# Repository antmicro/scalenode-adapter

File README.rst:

=================
Scalenode Adapter
=================

Copyright (c) 2021 `Antmicro <https://www.antmicro.com>`_

.. figure:: img/scalenode-adapter.png

Overview
--------

This repository contains design files of the expansion card for the Antmicro's `Scalenode <https://github.com/antmicro/scalenode>`_ platform.
This expansion card exposes three USB host ports with independent supply current monitoring for each port.
This allows for using the Scalenode to interact with external, FPGA-driven evaluation boards such as the Digilent `Arty A7 <https://reference.digilentinc.com/programmable-logic/arty/start>`_ boards.
The design files were prepared in KiCad.
An initial production release for the design was fabricated as prototypes and these are now being tested.

Repository structure
--------------------
The main repository directory contains KiCad PCB project files, a LICENSE and README.
The remaining files are stored in the following directories:

* ``lib`` - contains the component libraries
* ``img`` - contains graphics for this README

Key Features
------------

* Expansion board for the Scalenode module
* Supports up to three Digilet Arty boards
* On-board current measurement circuitry

License
=======

`Apache-2.0 <LICENSE>`_

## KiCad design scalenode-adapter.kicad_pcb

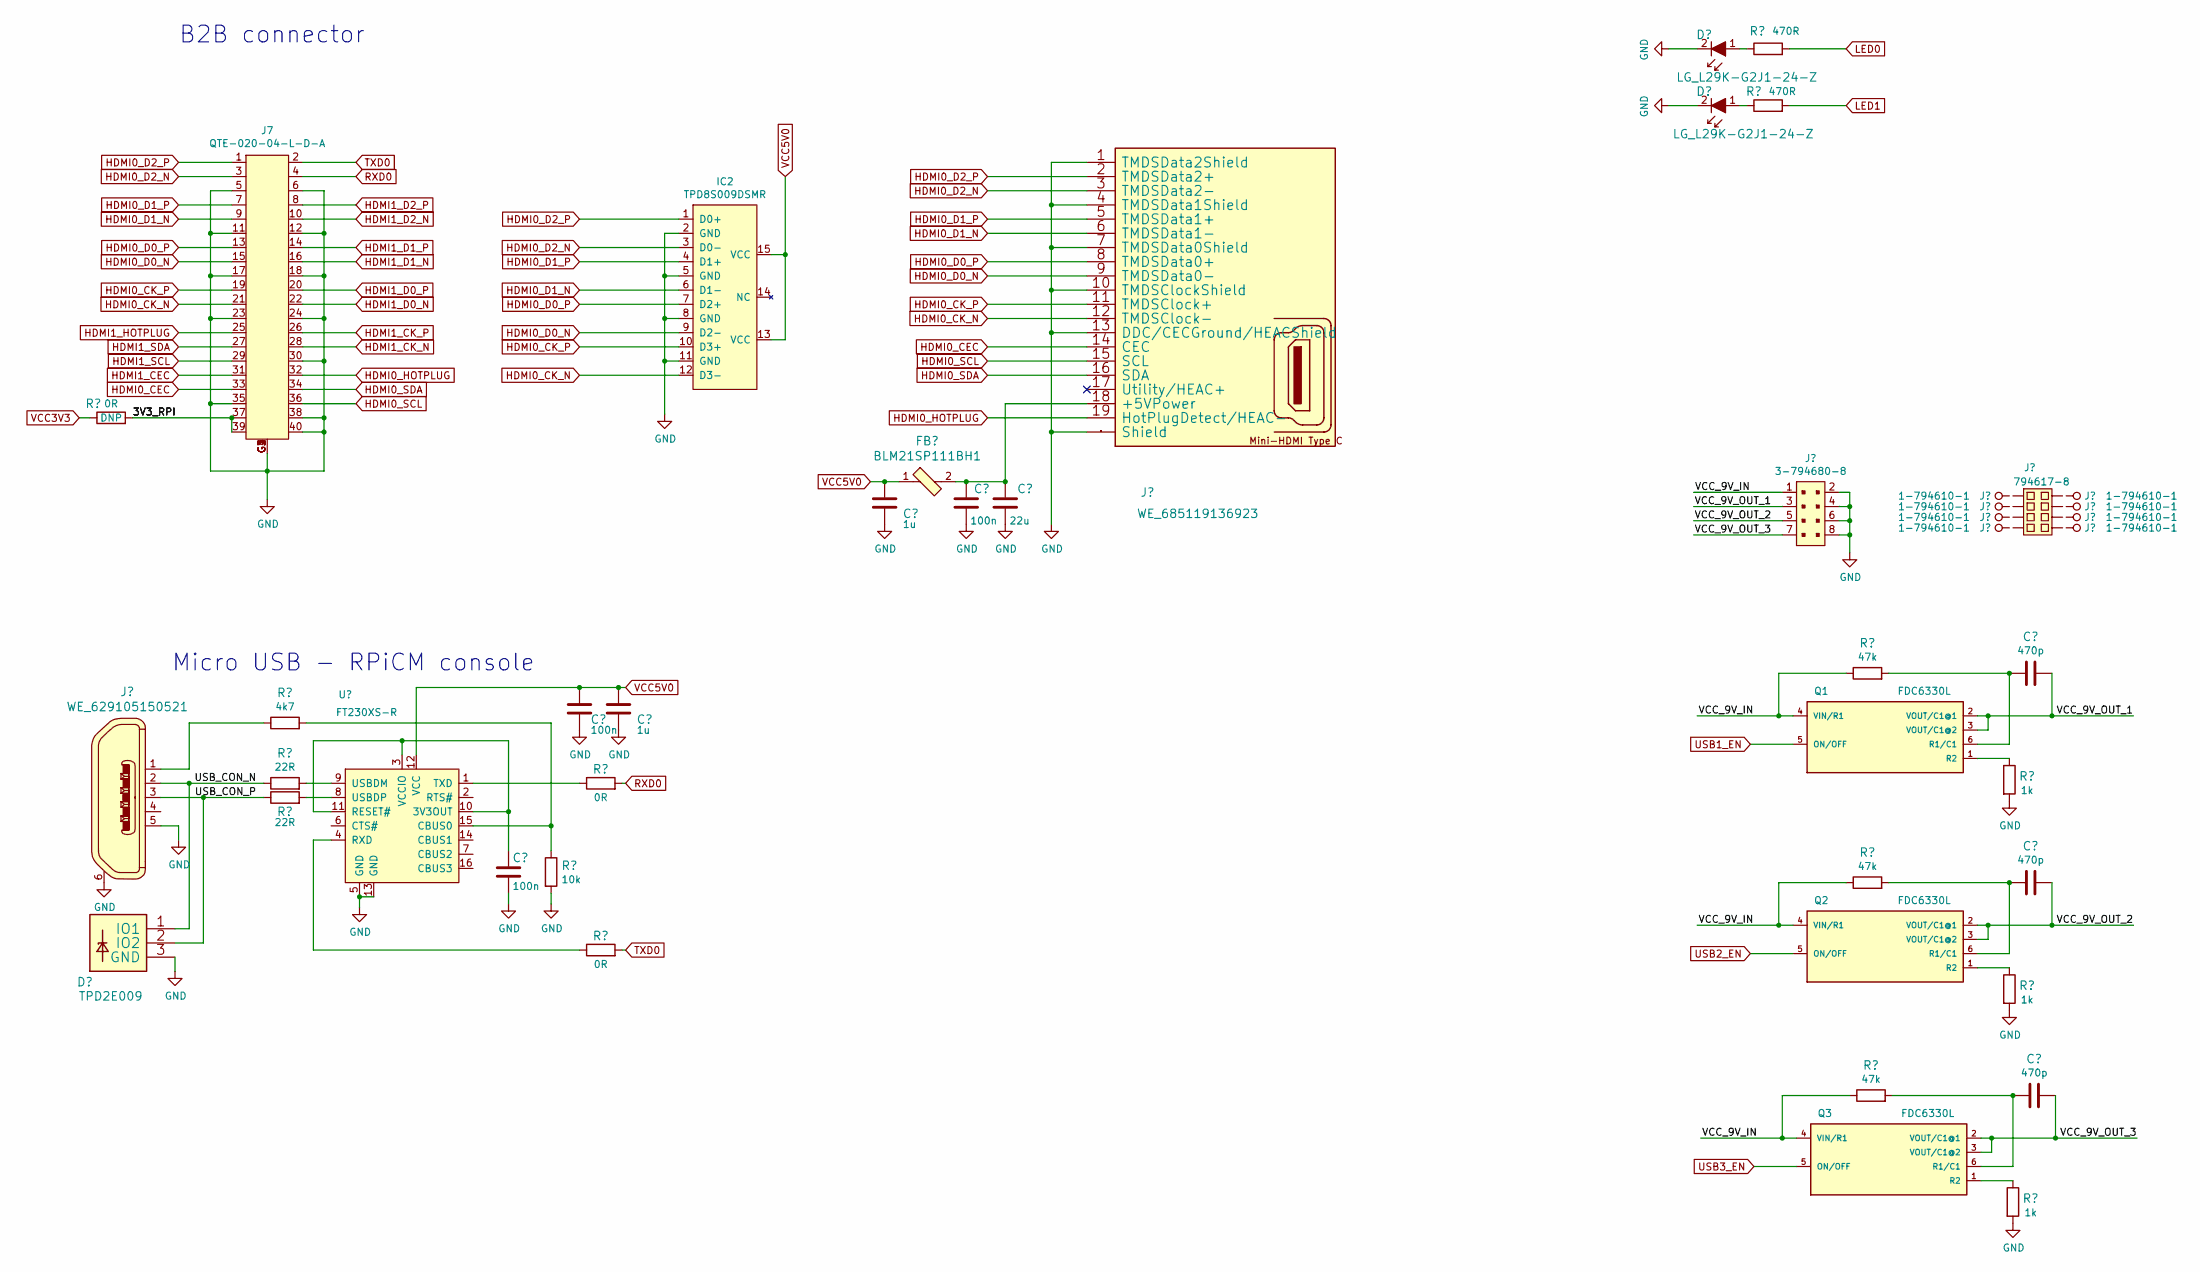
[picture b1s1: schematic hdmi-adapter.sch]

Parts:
C49, C50, C53: C_100n_0402; 0402-cap; MPN 0402X104K6R3CT
C51, C52: C_1u_0402; 0402-cap; MPN C1005X6S1A105K050BC
C54: C_22u_0603; 0603-cap; MPN GRM188R60J226MEA0D
D8, D9: LG_L29K-G2J1-24-Z; LED_0603; MPN LG L29K-G2J1-24-Z
D10: TPD2E009; SOT-3; MPN TPD2E009DRTR
FB2: BLM21SP111BH1; 0805-res; MPN BLM21SP111BH1D
IC2: TPD8S009DSMR; R-PDSO-N15; MPN TPD8S009DSMR
J7: QTE-020-04-L-D-A; MPN QTE-020-04-L-D-A
J8: WE_629105150521; USB_Micro_B_Female_629105150521; MPN 629105150521
Q1, Q2, Q3: FDC6330L; MPN FDC6330L
R37: R_0R_0805; 0805-res; MPN CRCW08050000Z0EA
R38, R39: R_470R_0402; 0402-res; MPN CRCW0402470RFKED
R47, R48, R49: R_1k_0402; 0402-res; MPN CR0402-FX-1001GLF

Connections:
/antartix hdmi adapter/3V3_RPI: J7.37, J7.39, R37.2
/antartix hdmi adapter/USB_CON_N: D10.1 (IO1), J8.2; also elsewhere on the board
/antartix hdmi adapter/USB_CON_P: D10.2 (IO2), J8.3; also elsewhere on the board
/antartix hdmi adapter/VCC_9V_IN: Q1.4 (VIN/R1), Q2.4 (VIN/R1), Q3.4 (VIN/R1); also elsewhere on the board
/antartix hdmi adapter/VCC_9V_OUT_1: Q1.2 (VOUT/C1@1), Q1.3 (VOUT/C1@2); also elsewhere on the board
/antartix hdmi adapter/VCC_9V_OUT_2: Q2.2 (VOUT/C1@1), Q2.3 (VOUT/C1@2); also elsewhere on the board
/antartix hdmi adapter/VCC_9V_OUT_3: Q3.2 (VOUT/C1@1), Q3.3 (VOUT/C1@2); also elsewhere on the board
GND: C49.2, C50.2, C51.2, C52.2, C53.2, C54.1, D8.2, D9.2, D10.3 (GND), IC2.2 (GND), IC2.5 (GND), IC2.8 (GND), IC2.11 (GND), J7.5, J7.6, J7.11, J7.12, J7.17, J7.18, J7.23, J7.24, J7.30, J7.35, J7.38, J7.40, J7.G1, J7.G2, J7.G3, J7.G4, J8.5, J8.6, R47.2, R48.2, R49.2; also elsewhere on the board
HDMI0_CEC: J7.33; also elsewhere on the board
HDMI0_CK_N: IC2.12 (D3-), J7.21; also elsewhere on the board
HDMI0_CK_P: IC2.10 (D3+), J7.19; also elsewhere on the board
HDMI0_D0_N: IC2.9 (D2-), J7.15; also elsewhere on the board
HDMI0_D0_P: IC2.7 (D2+), J7.13; also elsewhere on the board
HDMI0_D1_N: IC2.6 (D1-), J7.9; also elsewhere on the board
HDMI0_D1_P: IC2.4 (D1+), J7.7; also elsewhere on the board
HDMI0_D2_N: IC2.3 (D0-), J7.3; also elsewhere on the board
HDMI0_D2_P: IC2.1 (D0+), J7.1; also elsewhere on the board
HDMI0_HOTPLUG: J7.32; also elsewhere on the board
HDMI0_SCL: J7.36; also elsewhere on the board
HDMI0_SDA: J7.34; also elsewhere on the board
HDMI1_CEC: J7.31
HDMI1_CK_N: J7.28
HDMI1_CK_P: J7.26
HDMI1_D0_N: J7.22
HDMI1_D0_P: J7.20
HDMI1_D1_N: J7.16
HDMI1_D1_P: J7.14
HDMI1_D2_N: J7.10
HDMI1_D2_P: J7.8
HDMI1_HOTPLUG: J7.25
HDMI1_SCL: J7.29
HDMI1_SDA: J7.27
LED0: R38.2; also elsewhere on the board
LED1: R39.2; also elsewhere on the board
unnamed 66: C49.1; also elsewhere on the board
unnamed 67: C53.1, C54.2, FB2.2; also elsewhere on the board
unnamed 68: Q1.6 (R1/C1); also elsewhere on the board
unnamed 69: Q2.6 (R1/C1); also elsewhere on the board
unnamed 70: Q3.6 (R1/C1); also elsewhere on the board
unnamed: D8.1, R38.1
unnamed: D9.1, R39.1
unnamed 124: J8.1; also elsewhere on the board
unnamed: Q1.1 (R2), R47.1
unnamed: Q2.1 (R2), R48.1
unnamed: Q3.1 (R2), R49.1
RXD0: J7.4; also elsewhere on the board
TXD0: J7.2; also elsewhere on the board
USB1_EN: Q1.5 (ON/OFF); also elsewhere on the board
USB2_EN: Q2.5 (ON/OFF); also elsewhere on the board
USB3_EN: Q3.5 (ON/OFF); also elsewhere on the board
VCC3V3: R37.1; also elsewhere on the board
VCC5V0: C50.1, C51.1, C52.1, FB2.1, IC2.13 (VCC), IC2.15 (VCC); also elsewhere on the board

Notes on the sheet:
B2B connector
Micro USB - RPiCM console

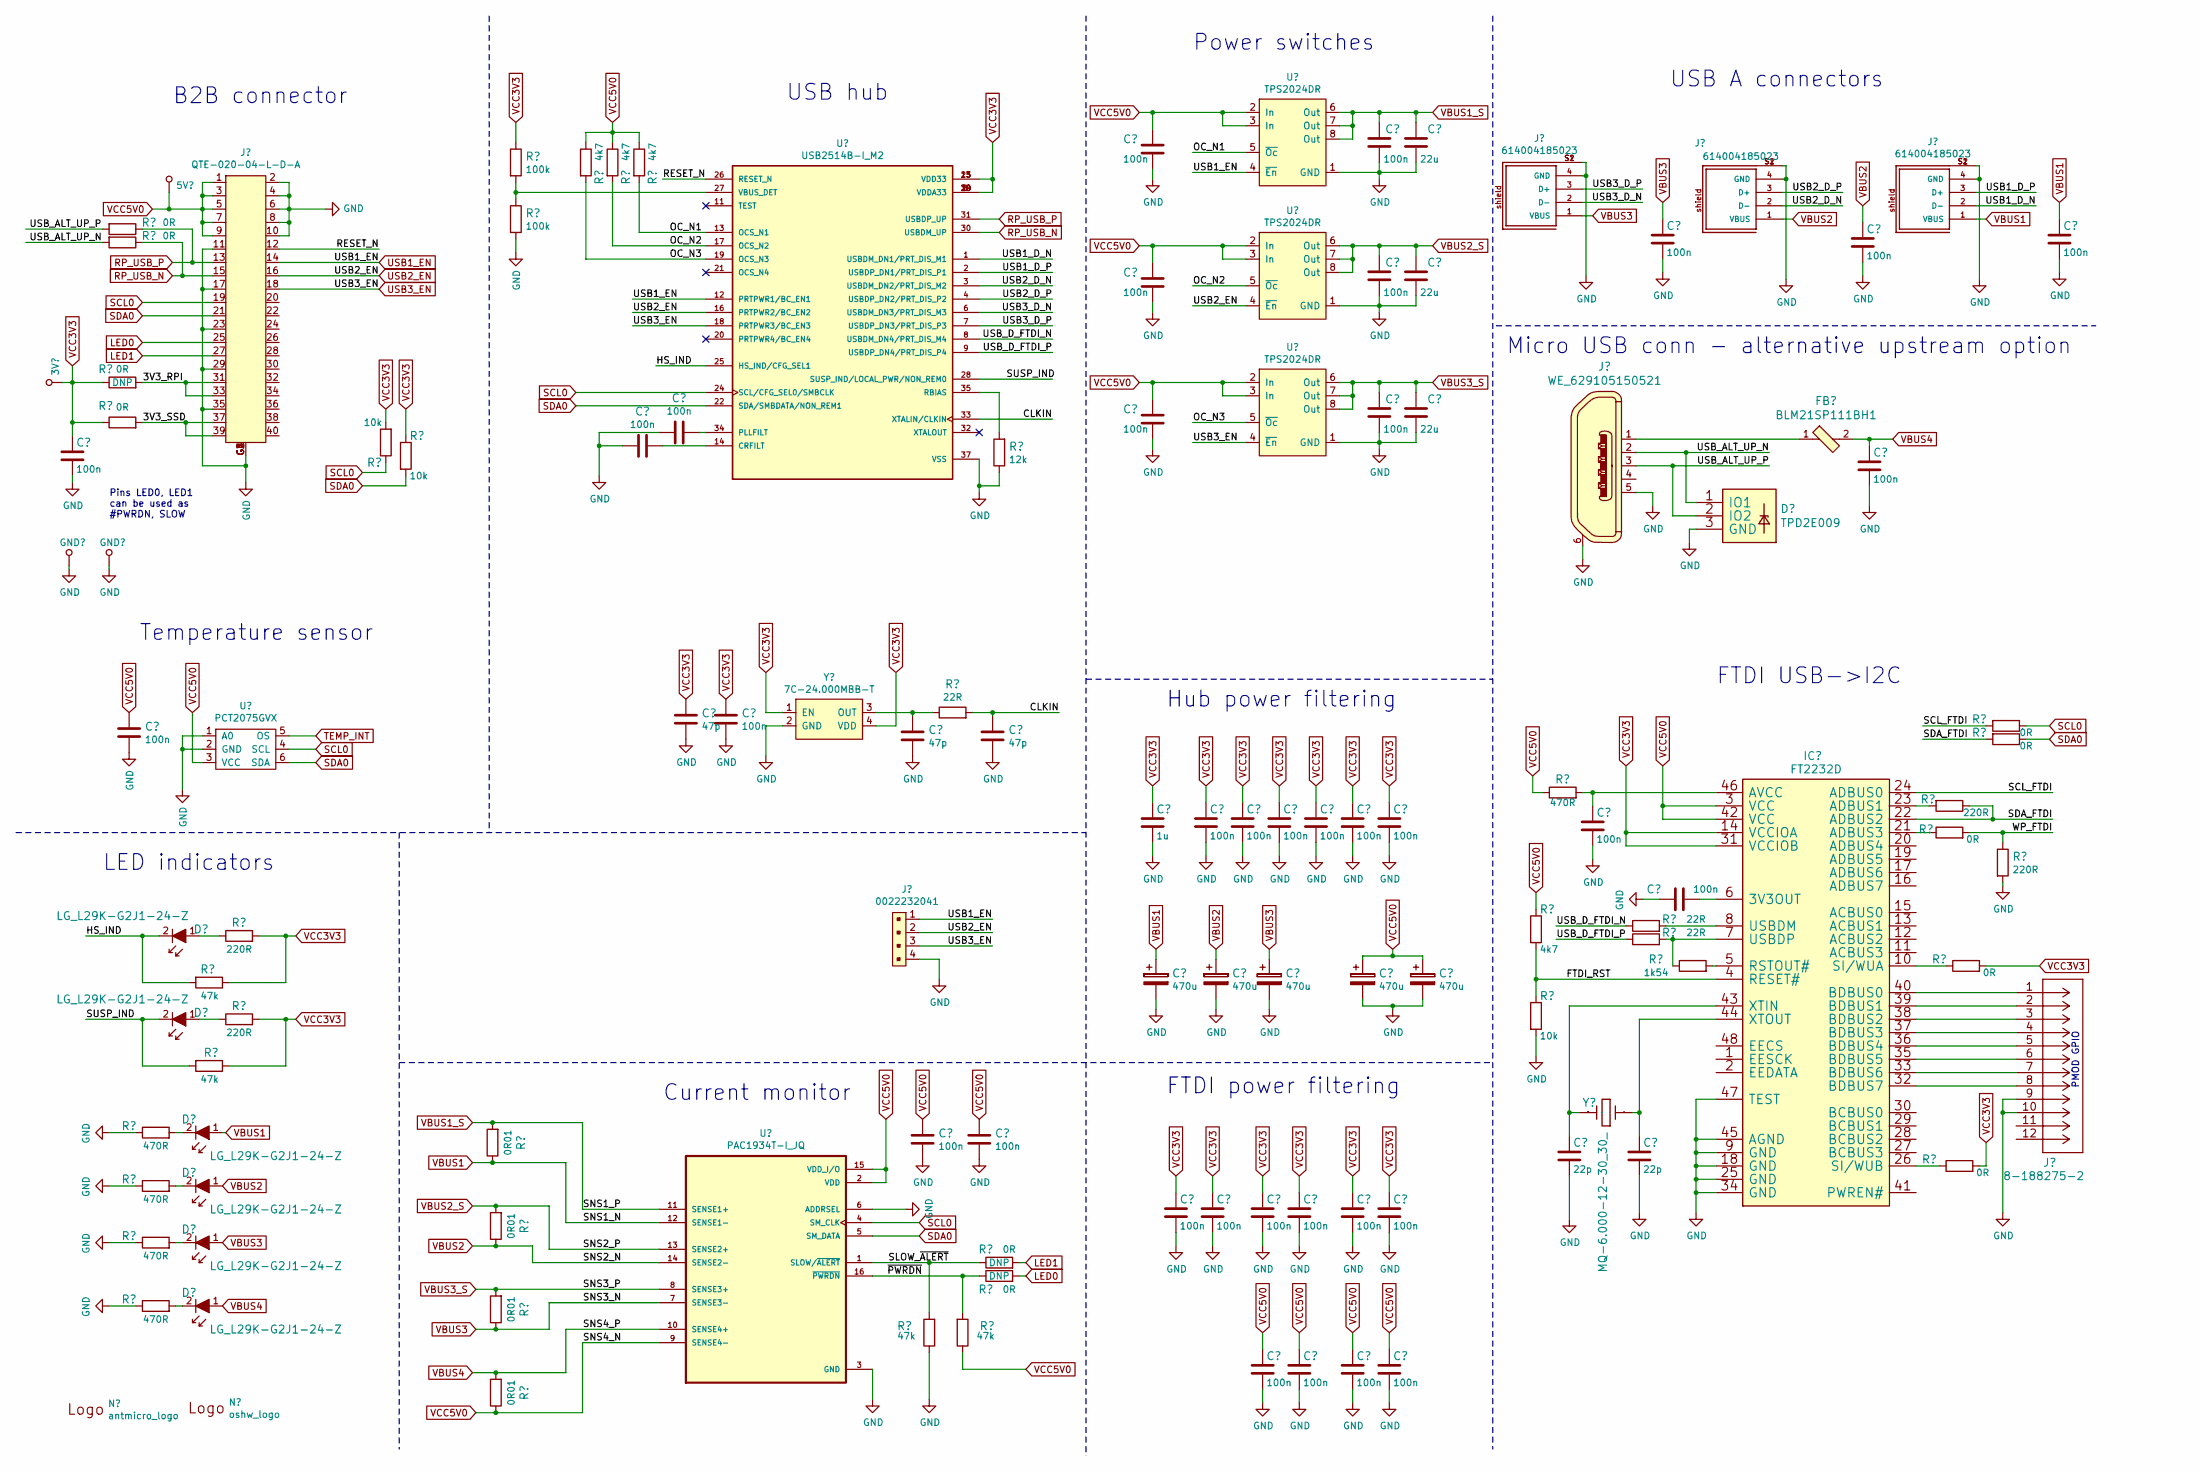
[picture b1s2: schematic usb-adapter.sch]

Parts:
3V1, 5V1: TP_SMD1MM; Testpoint_smd_1mm
C1, C2, C3, C4, C6, C9, C15, C16, C17, C19, C20, C21, C23, C24, C25, C26, C27, C28, C29, C31, C32, C33, C34, C35, C36, C42, C44, C45, C46, C47, C48, C58: C_100n_0402; 0402-cap; MPN 0402X104K6R3CT
C5, C7, C8: C_47p_0402; 0402-cap; MPN C0402C470J5GACTU
C10, C11, C12: C_100n_0603; 0603-cap; MPN 0603YC104KAZ2A
C13: C_1u_0402; 0402-cap; MPN C1005X6S1A105K050BC
C14, C18, C22, C30, C40: C_470u_KEMET_D; KEMET_D; MPN TR3D477M6R3C0200
C37, C38, C39: C_22u_0603; 0603-cap; MPN GRM188R60J226MEA0D
C41, C43: C_22p_0402; 0402-cap; MPN CC0402JRNPO9BN220
D1, D2, D3, D4, D5, D6: LG_L29K-G2J1-24-Z; LED_0603; MPN LG L29K-G2J1-24-Z
D7: TPD2E009; SOT-3; MPN TPD2E009DRTR
FB1: BLM21SP111BH1; 0805-res; MPN BLM21SP111BH1D
GND1, GND2: TP_SMD1MM; Testpoint_smd_1mm
IC1: FT2232D; LQFP-48_7x7mm; MPN FT2232D-REEL
J1: QTE-020-04-L-D-A; MPN QTE-020-04-L-D-A
J2: 0022232041; PinHeader_1x4_P2.54mm_Drill1.02mm; MPN 0022232041
J3, J5, J6: 614004185023; MPN 614004185023
J4: WE_629105150521; USB_Micro_B_Female_629105150521; MPN 629105150521
N1: antmicro_logo; antmicro-logo_scaled_15mm
N2: oshw_logo; oshw-logo
R1, R2, R31, R32, R33, R35, R36: R_0R_0402; 0402-res; MPN ERJ2GE0R00X
R3, R4: R_0R_0805; 0805-res; MPN CRCW08050000Z0EA
R5, R6, R7, R8, R28: R_470R_0402; 0402-res; MPN CRCW0402470RFKED
R9, R10, R50, R51: R_47k_0402; 0402-res; MPN MCMR04X4702FTL
R11, R12, R30, R34: R_220R_0402; 0402-res; MPN ERJ2GEJ221X
R13, R14, R27: R_10k_0402; 0402-res; MPN CRCW040210K0FKEDHP
R15, R16, R21, R22: R_0R01_1206; 1206-res; MPN ERJMP2KF10MU
R17, R18: R_100k_0402; 0402-res; MPN CRCW0402100KFKEDHP
R19, R20, R23, R26: R_4k7_0402; 0402-res; MPN ERJ2GEJ472X
R24, R56, R57: R_22R_0402; 0402-res; MPN CRCW040222R0FKED
R25: R_12k_0402; 0402-res; MPN CRCW040212K0FKEDHP
R29: R_1k54_0402; 0402-res; MPN CRCW04021K54FKED.
U1: PCT2075GVX; SOT95P275X110-6N; MPN PCT2075GVX
U2: PAC1934T-I_JQ; QFN65P400X400X55-17N
U3: USB2514B-I_M2; QFN50P600X600X100-37N; MPN USB2514B-I/M2
U4, U5, U6: TPS2024DR; SOIC-8_W3.9mm; MPN TPS2024DR
Y1: 7C-24.000MBB-T; MPN 7C-24.000MBB-T
Y2: MQ-6.000-12-30_30_; Crystal_5x7mm; MPN MQ-6.000-12-30/30/-40+85

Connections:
/antartix usb adapter/3V3_RPI: J1.31, J1.33, R3.2
/antartix usb adapter/3V3_SSD: J1.37, J1.39, R4.2
/antartix usb adapter/CLKIN: C8.1, R24.2, U3.33 (XTALIN/CLKIN)
/antartix usb adapter/FTDI_RST: IC1.4 (RESET#), R26.2, R27.1
/antartix usb adapter/HS_IND: D1.2, R9.2, U3.25 (HS_IND/CFG_SEL1)
/antartix usb adapter/OC_N1: R23.2, U3.13 (OCS_N1), U4.5 (~Oc)
/antartix usb adapter/OC_N2: R20.2, U3.17 (OCS_N2), U5.5 (~Oc)
/antartix usb adapter/OC_N3: R19.2, U3.19 (OCS_N3), U6.5 (~Oc)
/antartix usb adapter/RESET_N: J1.12, U3.26 (RESET_N)
/antartix usb adapter/SCL_FTDI: IC1.24 (ADBUS0), R35.2
/antartix usb adapter/SDA_FTDI: IC1.22 (ADBUS2), R30.1, R36.2
/antartix usb adapter/SLOW_~ALERT: R50.2, U2.1 (SLOW/~ALERT); also elsewhere on the board
/antartix usb adapter/SUSP_IND: D2.2, R10.2, U3.28 (SUSP_IND/LOCAL_PWR/NON_REM0)
/antartix usb adapter/USB1_D_N: J6.2 (D-), U3.1 (USBDM_DN1/PRT_DIS_M1)
/antartix usb adapter/USB1_D_P: J6.3 (D+), U3.2 (USBDP_DN1/PRT_DIS_P1)
/antartix usb adapter/USB2_D_N: J5.2 (D-), U3.3 (USBDM_DN2/PRT_DIS_M2)
/antartix usb adapter/USB2_D_P: J5.3 (D+), U3.4 (USBDP_DN2/PRT_DIS_P2)
/antartix usb adapter/USB3_D_N: J3.2 (D-), U3.6 (USBDM_DN3/PRT_DIS_M3)
/antartix usb adapter/USB3_D_P: J3.3 (D+), U3.7 (USBDP_DN3/PRT_DIS_P3)
/antartix usb adapter/USB_ALT_UP_N: D7.1 (IO1), J4.2, R2.2
/antartix usb adapter/USB_ALT_UP_P: D7.2 (IO2), J4.3, R1.2
/antartix usb adapter/USB_D_FTDI_N: R56.1, U3.8 (USBDM_DN4/PRT_DIS_M4)
/antartix usb adapter/USB_D_FTDI_P: R57.1, U3.9 (USBDP_DN4/PRT_DIS_P4)
/antartix usb adapter/WP_FTDI: R31.2, R34.1
/antartix usb adapter/~PWRDN: R51.2, U2.16 (~PWRDN); also elsewhere on the board
GND: C1.2, C2.2, C3.2, C4.2, C5.2, C6.2, C7.2, C8.2, C9.2, C10.2, C11.2, C12.2, C13.2, C14.2, C15.2, C16.2, C17.2, C18.2, C19.2, C20.2, C21.2, C22.2, C23.2, C24.2, C25.2, C26.2, C27.2, C28.2, C29.2, C30.2, C31.1, C32.1, C33.1, C34.2, C35.2, C36.2, C37.1, C38.1, C39.1, C40.2, C41.2, C42.2, C43.2, C44.2, C45.2, C46.2, C47.2, C48.2, C58.2, D7.3 (GND), GND1.1, GND2.1, IC1.9 (GND), IC1.18 (GND), IC1.25 (GND), IC1.34 (GND), IC1.45 (AGND), IC1.47 (TEST), J1.2, J1.4, J1.6, J1.8, J1.10, J1.11, J1.17, J1.23, J1.29, J1.35, J1.G1, J1.G2, J1.G3, J1.G4, J2.4, J3.4 (GND), J3.S1, J3.S2, J4.5, J4.6, J5.4 (GND), J5.S1, J5.S2, J6.4 (GND), J6.S1, J6.S2, R5.1, R6.1, R7.1, R8.1, R18.2, R25.1, R27.2, R34.2, R50.1, U1.1 (A0), U1.2 (GND), U2.3 (GND), U2.6 (ADDRSEL), U2.17, U3.37 (VSS), U4.1 (GND), U5.1 (GND), U6.1 (GND), Y1.2 (GND); also elsewhere on the board
LED0: J1.25; also elsewhere on the board
LED1: J1.27; also elsewhere on the board
unnamed: C3.1, U3.14 (CRFILT)
unnamed: C4.1, U3.34 (PLLFILT)
unnamed: C7.1, R24.1, Y1.3 (OUT)
unnamed: C41.1, IC1.43 (XTIN), Y2.1
unnamed: C42.1, IC1.46 (AVCC), R28.2
unnamed: C43.1, IC1.44 (XTOUT), Y2.3
unnamed: C45.1, IC1.6 (3V3OUT)
unnamed: D1.1, R11.1
unnamed: D2.1, R12.1
unnamed: D3.2, R5.2
unnamed: D4.2, R6.2
unnamed: D5.2, R7.2
unnamed: D6.2, R8.2
unnamed: FB1.1, J4.1
unnamed: IC1.5 (RSTOUT#), R29.2
unnamed: IC1.7 (USBDP), R29.1, R57.2
unnamed: IC1.8 (USBDM), R56.2
unnamed: IC1.10 (SI/WUA), R33.1
unnamed: IC1.21 (ADBUS3), R31.1
unnamed: IC1.23 (ADBUS1), R30.2
unnamed: IC1.26 (SI/WUB), R32.1
unnamed 101: IC1.32 (BDBUS7); also elsewhere on the board
unnamed 102: IC1.33 (BDBUS6); also elsewhere on the board
unnamed 103: IC1.35 (BDBUS5); also elsewhere on the board
unnamed 104: IC1.36 (BDBUS4); also elsewhere on the board
unnamed 105: IC1.37 (BDBUS3); also elsewhere on the board
unnamed 106: IC1.38 (BDBUS2); also elsewhere on the board
unnamed 107: IC1.39 (BDBUS1); also elsewhere on the board
unnamed 108: IC1.40 (BDBUS0); also elsewhere on the board
unnamed: R17.2, R18.1, U3.27 (VBUS_DET)
unnamed: R25.2, U3.35 (RBIAS)
RP_USB_N: J1.15, R2.1, U3.30 (USBDM_UP)
RP_USB_P: J1.13, R1.1, U3.31 (USBDP_UP)
SCL0: J1.19, R13.1, R35.1, U1.4 (SCL), U2.4 (SM_CLK), U3.24 (SCL/CFG_SEL0/SMBCLK)
SDA0: J1.21, R14.2, R36.1, U1.6 (SDA), U2.5 (SM_DATA), U3.22 (SDA/SMBDATA/NON_REM1)
TEMP_INT: U1.5 (OS)
USB1_EN: J1.14, J2.1, U3.12 (PRTPWR1/BC_EN1), U4.4 (~En); also elsewhere on the board
USB2_EN: J1.16, J2.2, U3.16 (PRTPWR2/BC_EN2), U5.4 (~En); also elsewhere on the board
USB3_EN: J1.18, J2.3, U3.18 (PRTPWR3/BC_EN3), U6.4 (~En); also elsewhere on the board
VBUS1: C14.1, C48.1, D3.1, J6.1 (VBUS), R15.1, U2.12 (SENSE1-)
VBUS1_S: C31.2, C37.2, R15.2, U2.11 (SENSE1+), U4.6 (Out), U4.7 (Out), U4.8 (Out)
VBUS2: C18.1, C46.1, D4.1, J5.1 (VBUS), R21.1, U2.14 (SENSE2-)
VBUS2_S: C32.2, C38.2, R21.2, U2.13 (SENSE2+), U5.6 (Out), U5.7 (Out), U5.8 (Out)
VBUS3: C22.1, C44.1, D5.1, J3.1 (VBUS), R16.1, U2.7 (SENSE3-)
VBUS3_S: C33.2, C39.2, R16.2, U2.8 (SENSE3+), U6.6 (Out), U6.7 (Out), U6.8 (Out)
VBUS4: C47.1, D6.1, FB1.2, R22.2, U2.10 (SENSE4+)
VCC3V3: 3V1.1, C1.1, C5.1, C6.1, C13.1, C15.1, C16.1, C17.1, C19.1, C20.1, C23.1, C24.1, C26.1, C27.1, C28.1, C34.1, C35.1, IC1.14 (VCCIOA), IC1.31 (VCCIOB), R3.1, R4.1, R9.1, R10.1, R11.2, R12.2, R13.2, R14.1, R17.1, R32.2, R33.2, U3.5 (VDDA33), U3.10 (VDDA33), U3.15 (VDD33), U3.23 (VDD33), U3.29 (VDDA33), U3.36 (VDDA33), Y1.1 (EN), Y1.4 (VDD); also elsewhere on the board
VCC5V0: 5V1.1, C2.1, C9.1, C10.1, C11.1, C12.1, C21.1, C25.1, C29.1, C30.1, C36.1, C40.1, C58.1, IC1.3 (VCC), IC1.42 (VCC), J1.1, J1.3, J1.5, J1.7, J1.9, R19.1, R20.1, R22.1, R23.1, R26.1, R28.1, R51.1, U1.3 (VCC), U2.2 (VDD), U2.9 (SENSE4-), U2.15 (VDD_I/O), U4.2 (In), U4.3 (In), U5.2 (In), U5.3 (In), U6.2 (In), U6.3 (In); also elsewhere on the board

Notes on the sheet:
Hub power filtering
Micro USB conn - alternative upstream option
FTDI power filtering
FTDI USB->I2C
USB A connectors
LED indicators
Power switches
Current monitor
USB hub
Temperature sensor
B2B connector
Pins LED0, LED1 can be used as #PWRDN, SLOW
PMOD GPIO

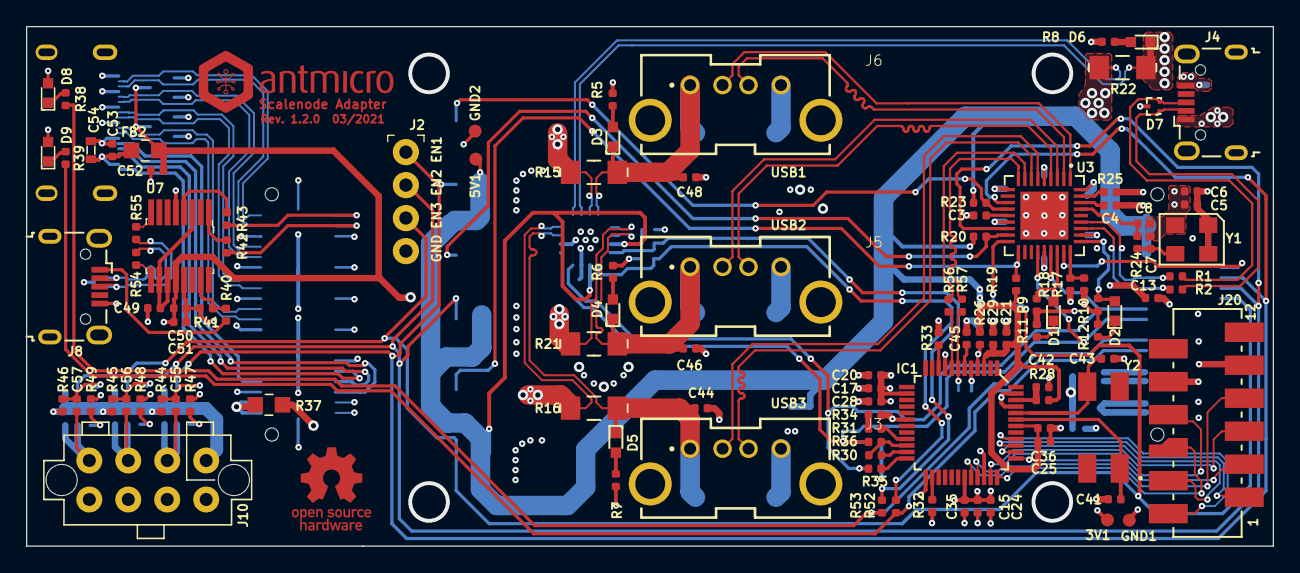
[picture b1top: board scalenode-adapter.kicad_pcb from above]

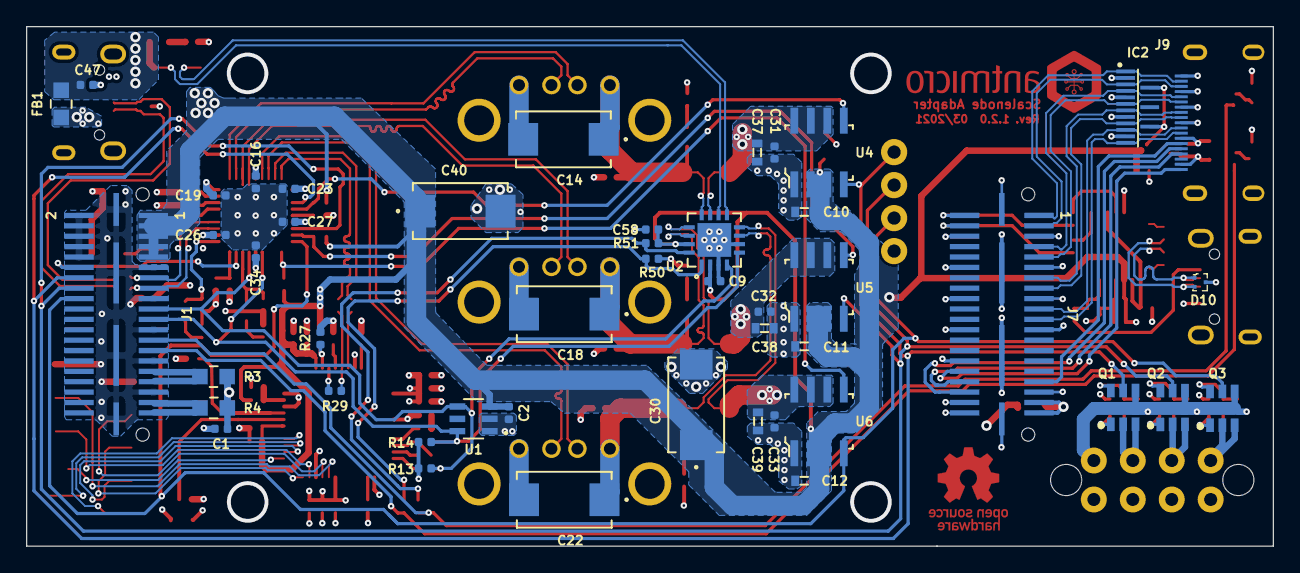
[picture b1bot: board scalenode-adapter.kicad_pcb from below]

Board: 4 copper layers, 96.0 x 40.0 mm, 167 parts (56 on the bottom side), 112 nets.

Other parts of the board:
C55, C56, C57: C_470p_0402; 0402-cap
J9: WE_685119136923
J10: 3-794680-8
J11, J12, J13, J14, J16, J17, J18, J19: 1-794610-1
J15: 794617-8; 3-794617-8
J20: 8-188275-2
R40: R_4k7_0402; 0402-res
R41: R_10k_0402; 0402-res
R42, R43, R52, R53: R_0R_0402; 0402-res
R44, R45, R46: R_47k_0402; 0402-res
R54, R55: R_22R_0402; 0402-res
U7: FT230XS-R; SSOP-16_W3.90mm

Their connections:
/antartix hdmi adapter/USB_CON_N: R54.1; also elsewhere on the board
/antartix hdmi adapter/USB_CON_P: R55.1; also elsewhere on the board
/antartix hdmi adapter/VCC_9V_IN: J10.1, R44.1, R45.1, R46.1; also elsewhere on the board
/antartix hdmi adapter/VCC_9V_OUT_1: C55.1, J10.3; also elsewhere on the board
/antartix hdmi adapter/VCC_9V_OUT_2: C56.1, J10.5; also elsewhere on the board
/antartix hdmi adapter/VCC_9V_OUT_3: C57.1, J10.7; also elsewhere on the board
/antartix usb adapter/SLOW_~ALERT: R52.1; also elsewhere on the board
/antartix usb adapter/~PWRDN: R53.1; also elsewhere on the board
GND: J9.1, J9.4, J9.7, J9.10, J9.13, J9.Shell, J10.2, J10.4, J10.6, J10.8, J20.9, J20.10, R41.2, U7.5, U7.13; also elsewhere on the board
HDMI0_CEC: J9.14; also elsewhere on the board
HDMI0_CK_N: J9.12; also elsewhere on the board
HDMI0_CK_P: J9.11; also elsewhere on the board
HDMI0_D0_N: J9.9; also elsewhere on the board
HDMI0_D0_P: J9.8; also elsewhere on the board
HDMI0_D1_N: J9.6; also elsewhere on the board
HDMI0_D1_P: J9.5; also elsewhere on the board
HDMI0_D2_N: J9.3; also elsewhere on the board
HDMI0_D2_P: J9.2; also elsewhere on the board
HDMI0_HOTPLUG: J9.19; also elsewhere on the board
HDMI0_SCL: J9.15; also elsewhere on the board
HDMI0_SDA: J9.16; also elsewhere on the board
LED0: R53.2; also elsewhere on the board
LED1: R52.2; also elsewhere on the board
unnamed 66: U7.3, U7.10, U7.11; also elsewhere on the board
unnamed 67: J9.18; also elsewhere on the board
unnamed 68: C55.2, R44.2; also elsewhere on the board
unnamed 69: C56.2, R45.2; also elsewhere on the board
unnamed 70: C57.2, R46.2; also elsewhere on the board
unnamed 101: J20.8; also elsewhere on the board
unnamed 102: J20.7; also elsewhere on the board
unnamed 103: J20.6; also elsewhere on the board
unnamed 104: J20.5; also elsewhere on the board
unnamed 105: J20.4; also elsewhere on the board
unnamed 106: J20.3; also elsewhere on the board
unnamed 107: J20.2; also elsewhere on the board
unnamed 108: J20.1; also elsewhere on the board
unnamed 124: R40.1; also elsewhere on the board
unnamed: R40.2, R41.1, U7.15
unnamed: R42.1, U7.1
unnamed: R43.1, U7.4
unnamed: R54.2, U7.9
unnamed: R55.2, U7.8
RXD0: R42.2; also elsewhere on the board
TXD0: R43.2; also elsewhere on the board
VCC5V0: U7.12; also elsewhere on the board

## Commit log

2021-08-16 Initial commit. Add initial design files
2021-08-16 Add power switches, add current monitor circuits
2021-08-16 Update schematic
2021-08-16 Add 3x vertical USB connector
2021-08-16 Fix outline
2021-08-16 Add changes to schematic
    -Add pull up resistors on I2C
    -Add Voltage devider on VBUS_DET
    -Add Hi-Speed upstream port indicator LED
2021-08-16 Add FTDI and clean up schematic
2021-08-16 Add initial component placement
2021-08-16 Update PCB outline
2021-08-16 Update current monitoring circuit
2021-08-16 Layout update (WIP)
2021-08-16 Add lib tables
2021-08-16 Fix optional micro USB connection
2021-08-16 Problem with power switches
2021-08-16 Modified layout, routed USB. Now routing current sensing
2021-08-16 Replace power switches
2021-08-16 Component placement done
2021-08-16 Layout done
2021-08-16 Routing control signals
2021-08-16 Board routed
2021-08-16 Remove redundant 3V3 traces
2021-08-16 Combine schematic sheets - Initial commit of the next PCB revision
2021-08-16 Add aux power supply to the schematic sheet
2021-08-16 Rename alt upstream lanes
2021-08-16 Add component placement
2021-08-16 Remove second HDMI and add LEDs to schematic
2021-08-16 Add hierarchical structure
2021-08-16 review amendments
2021-08-16 Connect UART(GPIO14 & GPIO15)to BDBUS of FTDI
2021-08-16 Add FTDI and LEDs
2021-08-16 Add HDMI control signals, change connector to mini HDMI
2021-08-16 Fix power keys
2021-08-16 Change aux power connector
2021-08-16 Reduce board size, update connector placement
2021-08-16 Route buttons and HDMI
2021-08-16 Route console and HDMI control signals
2021-08-16 Add 22R to FTDI
2021-08-16 Place logotypes on PCB
2021-08-16 Remove TXD1 and RXD1 labels
2021-08-16 Redesign HDMI and Micro USB layout
2021-08-16 Remove redundant spacers and 3D model of additional conenctor
2021-08-16 Clean the designators
2021-08-16 Add local libraries
2021-08-16 Update libraries fields
2021-08-16 Add MPNs
2021-08-16 Add BOMs
2021-08-16 Added micromatch-12 connector as PMOD GPIO. Bumped to 1.2.0
2021-08-16 Update naming convention
2021-08-16 Add README
2021-08-16 Connect EP of U2 to GND to resolve DRC
2021-08-16 Add LICENSE
2021-08-16 Resolve annular ring DRC issues
2021-08-16 README: Add links
2021-08-16 Assign revision code to schematic sheets

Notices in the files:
parts and their libraries:
Copyright 2016 Accelerated Designs. All rights reserved.
